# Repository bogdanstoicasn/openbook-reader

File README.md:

# OpenBook-reader

## Overview

OpenBook is an open-source e-book reader designed to be affordable and customizable. It is built around the ESP32-C6 microcontroller and integrates an E-Ink display, a Li-Po battery, and a microSD slot for extended storage. The device targets a wide range of users, from hobbyists to developers, who want to create their own e-book reader or modify existing designs.

## Table of Contents

1. [Features](#features)

2. [Data](#data)

3. [Block Diagram](#block-diagram)

4. [Hardware Functionality](#hardware-functionality)

5. [Hardware Components & Datasheets](#hardware-components--datasheets)

6. [Implementation](#implementation)

7. [Design Decisions and Trade-offs](#design-decisions-and-trade-offs)

8. [3D Visualizations](#3d-visualizations)
   
9. [Testing and Debugging](#testing-and-debugging)

10. [Suggestions](#suggestions)

## Features

- **Microcontroller**: ESP32-C6 with Wi-Fi and Bluetooth capabilities

- **Display**: 7.5" E-Ink display with a resolution of  800x480 pixels

- **Storage**: MicroSD card slot for additional storage

- **Battery**: Rechargeable Li-Po battery with a capacity of 2500mAh

- **Connectivity**: Wi-Fi 6, Bluetooth 5.0, and USB-C for charging and data transfer

- **Sensors**: Integrated environmental sensor (BME680) for temperature, humidity, pressure, and gas measurements

- **Real-Time Clock**: DS3231 for accurate timekeeping

- **User Interface**: 3 tactile buttons for navigation and control

## Data

Dimension: 175mm x 114mm x 10mm

Weight: 250g
Supported file formats: EPUB, PDF, TXT, FB2.

Operating system: FreeRTOS

Charging: 5V/1A via USB-C

## Block Diagram

## Hardware Functionality

### Microcontroller:

The ESP32-C6 is the main processing unit, responsible for handling all system operations, including e-paper display updates, wireless communication, and power management. It features:

- RISC-V architecture 32-bit core

- 2.4 GHz Wi-Fi and Bluetooth 5.0 connectivity

-  160 MHz clock speed with 4 stage pipeline

- L1 chache 16KB

- ROM 320KB

- SRAM 512KB(HP) + 16KB (LP)

- 30 GPIO pins

Power consumption: 160uA in deep sleep mode, 10mA in active mode

### Display:

- Type: E-Ink (E-Paper) display

- Size: 7.5 inches

- Resolution:  800x480 pixels

- Communication: SPI interface

- Power consumption: ~1.2mW in active mode, ~0.1mW in standby mode

Connection to the ESP32-C6 and other modules:

> IO7 -> MOSI(14)

> IO6 -> SCK(13)

> IO10 -> EPD_CS(12)

> IO5 -> EPD_DC(11)

> IO23 -> EPD_RST(10)

> IO3 -> EPD_BUSY(9)

Connection to power:

> EPD_3V3 -> 3.3V

### MicroSD Card

- Type: MicroSD card

- Capacity: Up to 32GB (FAT32 format)

- Communication: SPI interface

- Power consumption: ~50mA during read/write operations, ~10uA in standby mode

Connection to the ESP32-C6 and other modules:

> IO7 -> MOSI(CMD)

> IO6 -> SCK(CLK)

> IO4 -> SS_SD(CD/DAT3)

> IO2 -> MISO(DAT0)

### Battery and Power Management

- Type: Li-Po battery

- Capacity: 2500mAh

- Voltage: 3.7V nominal, 4.2V max

- Voltage regulator: MCP73831T for charging and power management

- Charging: 5V/1A via USB-C

- Power consumption: ~10mA during active mode, less than 50uA in deep sleep mode

Connection to the ESP32-C6 and other modules:

> CELL -> BAT

> IO21 -> SDA(SDA)

> IO22 -> SCL(SCL)

### Environmental Sensor

- Type: BME680

- Measurement: Temperature, humidity, pressure, and gas

- Communication: I2C interface

- Power consumption: ~3.6mA during measurement, ~0.1uA in sleep mode

Connection to the ESP32-C6 and other modules:

> IO21 -> SDA(SDI)

> IO22 -> SCL(SCK)

> IO19 -> I2C_PW(VDDIO)

### Real-Time Clock

- Type: DS3231

- Function: Accurate timekeeping

- Communication: I2C interface

- Power consumption: ~1.5uA in battery backup mode, ~0.1uA in sleep mode

Connection to the ESP32-C6 and other modules:

> IO21 -> SDA(15)

> IO22 -> SCL(16)

> IO18 -> RTC_RST(RST)

> IO1 -> 32KHz(32KHz)

> IO0 -> INT_RTC(SQW/INT)

### External Nor Flash

- Type: SPI Flash

- Capacity: 64MB

- Communication: SPI interface

- Power consumption: ~10mA during read/write operations, ~0.1uA in standby mode

Connection to the ESP32-C6 and other modules:

> IO11 -> EPD_CS(CS)

> IO6 -> SCK(CLK)

> IO2 -> MISO(DO/IO1)

> IO7 -> MOSI(DI/IO0)

### USB-C Connector

- Type: USB-C connector

- Function: Charging and data transfer

- Power consumption: ~5V/1A during charging, ~0.1uA in standby mode

- Protection: PFMF varistor for ESD protection

- Diode: Schottky barrier rectifier diode for reverse polarity protection

### Buttons

- Type: Tactile push buttons

- Number: 3

- Function: User input for navigation and control

Connection to the ESP32-C6 and other modules:

> EN -> RESET

> IO9 -> IO/BOOT

> IO15 -> IO/CHANGE

### Calculations

| Component | Current Draw (mA) | Voltage (V) | Power (mW) |
|-----------|-------------------|-------------|------------|
| ESP32-C6  | 10 | 3.3         | 33         |
| E-Ink Display | 1.2 | 3.3         | 3.96       |
| MicroSD Card | 50 | 3.3         | 165        |
| BME680 | 3.6 | 3.3         | 11.88      |
| DS3231 | 0.015 | 3.3         | 0.0495     |
| MCP73831T | 10 | 3.3         | 33         |
| USB-C Connector | 5 | 5         | 25         |
| External Flash | 10 | 3.3         | 33         |

Total Power Consumption: 304.3 mW
Total Current Draw: 89.8 mA

## Hardware Components & Datasheets

| Name | Description | Num | Datasheet | Price |
|------|-------------|-----|-----------|-------|
| Micro-SD | Micro-Sd | 1 | https://www.attend.com.tw/data/download/file/112A-TAAR-R03_Spec.pdf | https://www.digikey.com/en/products/detail/attend-technology/112A-TAAR-R03/17633923 |
| Inductor | 68uH | 1 | https://www.we-online.com/components/products/datasheet/784373170680.pdf | https://eu.mouser.com/ProductDetail/Wurth-Elektronik/784373170680?qs=sGAEpiMZZMv126LJFLh8yzGkpireax1GgDeN9GF1EUQ%3D |
| Led | No description | 1 | https://www.bridgelux.com/sites/default/files/resource_media/DS51_Rev%20F%20Bridgelux%20SMD%203030%20Data%20sheet.pdf | https://www.digikey.com/en/products/detail/bridgelux/BXEM-27E0000-0-000/6618599 |
| Voltage Detector | With Adjustable Delay Time | 1 | https://www.rohm.com/datasheet?p=BD5229G&dist=Digi-key&media=referral&source=digi-key.com&campaign=Digi-key | https://www.digikey.com/en/products/detail/rohm-semiconductor/BD5229G-TR/658502?s=N4IgTCBcDaIEIBECsYwE4DiBaAKgJRAF0BfIA |
| Buttons | No description | 3 | https://configured-product-images.s3.amazonaws.com/Datasheets/TL3315.pdf | https://www.digikey.com/en/products/detail/e-switch/TL3315NF250Q/1870396 |
| Super Capacitor | 0.011F 3.3V | 1 | https://mm.digikey.com/Volume0/opasdata/d220001/medias/docus/6537/rev05-CPHCPM.pdf | https://www.digikey.com/en/products/detail/seiko-instruments/cph3225a/8692444 |
| Real Time Clock | Serial 16-Pin SOIC | 1 | https://www.analog.com/media/en/technical-documentation/data-sheets/DS3231.pdf | https://www.digikey.com/en/products/detail/analog-devices-inc-maxim-integrated/DS3231SN/1197576 |
| Capacitor | 8 x 100uF + 6 x 4.7 uF + 1uF x 11 + 1 x 10uF -> Check this capacitor series(look at capacitance code to buy from the specs)| 26 | https://eu.mouser.com/datasheet/2/40/cx5r_KGM-3223198.pdf | https://eu.mouser.com/ProductDetail/KYOCERA-AVX/0402YD104MAT2A?qs=4PckX6MNpMErOINbbZj3Cw%3D%3D&srsltid=AfmBOorRllqAGFDVGSlUxRe1HCu5DEMiSSNplU-KeE2woDnCuT1J4_ia |
| ESP32-C6-WROOM-1-N8 | Microcontroller of choice | 1 | https://www.espressif.com/sites/default/files/documentation/esp32-c6-wroom-1_wroom-1u_datasheet_en.pdf | https://www.digikey.com/en/products/detail/espressif-systems/ESP32-C6-WROOM-1-N8/17728866?utm_source=snapeda&utm_campaign=buynow&utm_medium=aggregator |
| Varsistor | Used in the USB Connector zone | 1 | https://ro.mouser.com/datasheet/2/358/typ_PFMF-1275918.pdf | https://ro.mouser.com/ProductDetail/Schurter/PFMF.050.2?qs=1auRipcfynCums5v1iucSA%3D%3D |
| Diode | Schottky Barrier Rectifier Diode | 2 | https://datasheets.kyocera-avx.com/schottky.pdf | https://www.digikey.com/en/products/detail/kyocera-avx/sd0805s020s1r0/3749517 |
| Integrated Environmental Unit | Sensor | 1 | https://www.bosch-sensortec.com/media/boschsensortec/downloads/datasheets/bst-bme680-ds001.pdf | https://www.digikey.com/en/products/detail/bosch-sensortec/bme680/7401317 |
| Resistor | Search on DigiKey 0402 smd resistor x (size). The link contains both the site to but from and the datasheet in the order from 'Num' coloumn. |5K1 x 1 + 100K x 1 + 10K x 16 + 0.47 x 1 + 2K x 1 + 200 x 1 + 15 x 1 | [https://www.yageo.com/upload/media/product/products/datasheet/rchip/PYu-RC_Group_51_RoHS_L_12.pdf](https://www.digikey.com/en/products/detail/yageo/RC0402FR-075K1L/726624) - https://www.digikey.com/en/products/detail/yageo/RC0402JR-07100KL/726416 - https://www.digikey.com/en/products/detail/yageo/RC0402JR-0710KL/726418 - https://www.digikey.com/en/products/detail/cts-resistor-products/73L1R47J/1543472 - https://www.digikey.com/en/products/detail/panasonic-electronic-components/ERJ-2RKF2001X/192194 - https://www.digikey.com/en/products/detail/panasonic-electronic-components/ERJ-2RKF2000X/192215 - https://www.digikey.com/en/products/detail/panasonic-electronic-components/ERJ-2RKF15R0X/192142 | Check the 'Datasheet' section |
| P-channel MOSFETs | DMG2305UX-7 | 2 | https://www.diodes.com/assets/Datasheets/DMG2305UX.pdf | https://www.digikey.com/en/products/detail/diodes-incorporated/DMG2305UX-7/4340667 | 
| Li-Ion, Li-Pol Controller | MCP73831T | 1 | https://ww1.microchip.com/downloads/en/DeviceDoc/MCP73831-Family-Data-Sheet-DS20001984H.pdf | https://www.digikey.com/en/products/detail/microchip-technology/MCP73831T-2ACI-OT/964301 |
| Hirose Connector | 24 Position FFC, FPC Connector Contacts, Top and Bottom 0.020" (0.50mm) Surface Mount, Right Angle | 1 | https://ro.mouser.com/datasheet/2/185/FH34SRJ_24S_0_5SH_99__CL0580_1255_6_99_2DDrawing_0-1615044.pdf | https://ro.mouser.com/ProductDetail/Hirose-Connector/FH34SRJ-24S-0.5SH99?qs=vcbW%252B4%252BSTIpKBl5ap9J8Fw%3D%3D |
| Battery Monitor IC | 3µA 1-Cell/2-Cell Fuel Gauge with ModelGauge | 1 | https://datasheets.maximintegrated.com/en/ds/MAX17048-MAX17049.pdf | https://www.digikey.com/en/products/detail/analog-devices-inc-maxim-integrated/MAX17048G-T10/3758921?utm_source=snapeda&utm_campaign=buynow&utm_medium=aggregator |
| Diode | DIODE, SCHOTTKY, 0.5A, 30V, SOD-123 | 3 | https://ro.mouser.com/datasheet/2/258/MBR0520_MBR0580_SOD123_-2492194.pdf | https://ro.mouser.com/ProductDetail/Micro-Commercial-Components-MCC/MBR0530-TP?qs=KFo7JewZbUECRHkxGanrdg%3D%3D&utm_id=6470900573&utm_source=google&utm_medium=cpc&utm_marketing_tactic=emeacorp&gad_source=1&gclid=CjwKCAjwwLO_BhB2EiwAx2e-3ydGTTX86bQDTTakfn6ATmKxw6Z5gldNGNQk4bDz2SK5HmB7sD0ZQxoCdvQQAvD_BwE&_gl=1*1n24ce1*_ga*MTM0NDU1MzYwMi4xNzQzMjYxMTcy*_ga_15W4STQT4T*MTc0MzU5MDMwOC41LjEuMTc0MzU5MjU2NS4xOC4wLjA. |
| Diode | ESD Suppressor Diode Polymer Bi-Dir 24V 150Vc 2-Pin Case 0603(1608Metric) T/R | 6 | https://www.littelfuse.com/assetdocs/pulseguard-esd-suppressors-pgb1-datasheet?assetguid=8a337998-d54d-466b-be4e-dc5bcd1f9321 | https://www.digikey.com/en/products/detail/littelfuse-inc/PGB1010603MR/715755?utm_source=snapeda&utm_campaign=buynow&utm_medium=aggregator |
| Qwiic Connector | SparkFun I2C Standard Qwiic Connector | 1 | Check https://www.sparkfun.com/qwiic | https://www.digikey.com/en/products/detail/onion-corporation/om-e-qwiic/9922970 |
| Capacitor | Polarized, 0.5pF ~ 100uF | 1 | https://ro.mouser.com/datasheet/2/281/1/GCQ1555C1HR50WB01_01A-3146956.pdf | https://ro.mouser.com/ProductDetail/Murata-Electronics/GCQ1555C1HR50WB01D?qs=0lQeLiL1qybSG%2FOlONlvIA%3D%3D |
| Connector USB | CONN USB 2.0 TYPE-C R/A SMT | 1 | https://gct.co/files/drawings/usb4110.pdf | https://eu.mouser.com/ProductDetail/GCT/USB4110-GF-A?qs=KUoIvG%2F9IlYiZvIXQjyJeA%3D%3D&utm_id=6470900573&utm_source=google&utm_medium=cpc&utm_marketing_tactic=emeacorp&gad_source=1&gclid=CjwKCAjwwLO_BhB2EiwAx2e-37JzTMkPOyYe_IgHkPGbT94lZUm900GBIAmoPtrMJZJCTbY6hQYkwBoChsQQAvD_BwE |
| N-channel MOSFETs | Mosfet N-Channel 30 V 1.4A (Tc) 400mW (Ta), 500mW (Tc) Surface Mount SC-70-3 (SI1308EDL-T1-GE3)| 1 | https://www.vishay.com/docs/63399/si1308edl.pdf | https://www.digikey.com/en/products/detail/vishay-siliconix/si1308edl-t1-ge3/4876435 |
| Solder Jumper | We can use 0 ohms resistor | 1 | https://industrial.panasonic.com/ww/products/pt/general-purpose-chip-resistors/models/ERJ2GE0R00X | https://www.digikey.com/en/products/detail/panasonic-electronic-components/ERJ-2GE0R00X/146727 |
| Test Pad | Testing points for the PCB (Adafruit). | 17 | https://analytics.supplyframe.com/trackingservlet/track/?r=0x34EY99PS_gIu2qWuzU9_U842M9-un2szqNoXX0OQ9lqbiEKGN3BJ73jgvlrgiXR89Peb0evqc4GXoUXllBhu1MMSvPYuTjdNvrqssrdYelKlOnXRLLdDb62WVGcgff9ScDqkaNl77wLfnOOEQKj2STWkPX13L-FNZ3oWIMFUHCC5-qDG-7Yig6Avs38Cl7gJvFvhhIZBQgwOTPSvwankeiqCZiPIu4pf1a70cDpS5iXBHs4MnmfZND2GG-sF6aJg5UUnsB5VhTJSE6wk45p-6HRTMw22O4bszSnP2Q-ZnkBbKsUJKjNCqwjgBsJDq1_QscdqTO6PxRf527DX_uye2RbWidMqOlR-Vbcwp2OFH8GWfRIZFBGLsZvpqmkT4i-YX6Nptn2BWY2qtOQUnzCPdCvB7YMhgJaZgpVomGW3xiBrXHrx7fYI1m3zFYuPc18lUM4dLxlLjbOFrCL0NYDVpEveG92dFwHfnYbXQgvjrXr2rAOwFVNwEcAFSYk5ktrRa9hExtgpErVY2QODMhmvQzib95lr7oG9joYEr_b8joW8nw_gi1w2cyDxUshEAF | https://componentsearchengine.com/prices/3825?manufacturer=Adafruit |

## Implementation

### Initial Setup and Tool Selection

- Choose your PCB design software(Fusion360)

- Prepare the mechanical dimensions and casing files provided

### Create the Schematic

- Add the ESP32-C6 microcontroller, power components, display interfaces, buttons, and other required components

- Ensure the pin configuration for the ESP32-C6 matches the required hardware interfaces (e.g., SPI for the display, I2C for sensors).

- Implement decoupling capacitors near the power pins

- Electrical Design Validation (EVT)

### PCB Layout Design

- Place major components like the ESP32, display, and battery connectors according to the provided layout recommendations

- Route the traces carefully, avoiding sharp angles and placing vias in non-critical signal paths

- Design Rule Check(DRC)

### Mechanical Design Integration

- Create 3D models for case, battery and display for integration

- Verify that all components fit within the casing and that connectors like USB and SD card slots align with physical cutouts

## Design Decisions and Trade-offs

- Decoupling capacitors(100nF) should be placed close to the power pins of major components.

- Power traces width: 0.3mm

- Power traces were routed without vias to ensure low impedance and reliable power delivery.

- Signal traces width: 0.15mm

- No routing under ESP antenna.

- 2 layers PCB with 2 ground planes.

- All components on TOP Layer.

- Test pads were placed close to the relevant signals to facilitate easier probing and debugging.

- PCB cut near ESP32-C6 antenna for better signal, with a keep-out zone to reduce interference.

- The ESP32-C6 features multiple low-power modes (including deep sleep and light sleep) and efficient power domain management.

- Via stitching under the ESP32-C6 is beneficial for improving thermal dissipation and electromagnetic interference (EMI) performance.

- The PCB layout follows the reference design shown in Images/layout_reference.pdf.

- All PCB traces are routed to avoid 90-degree angles to ensure signal integrity and reduce the risk of electromagnetic interference (EMI).

- The 3D connection model for the display has been designed to provide a realistic representation of the **Display**; however, the connection model it's not flexible(used just for accurate display representation).

- The models for the battery and display are included to mimic their real-world sizes for visualization purposes. They do not reflect the actual hardware functionality or internal components.

- Integrating ESD protection helps safeguard sensitive components—like the ESP32-C6 and display driver—from electrostatic discharge events

## 3D Visualizations

### PCB

### Battery

### Display

### Full Product

## Testing and Debugging

The OpenBook PCB has test pads for each major communication and power line.

1. TPRX - RX signal
2. TPTX - TX signal
3. TPVBAT - Battery voltage
4. 2 x TPGND - Ground
5. TP3V3 - 3.3V power
6. TPEPD_3V3 - EPD 3.3V power
7. TPMISO - MISO signal
8. TPMOSI - MOSI signal
9. TPSCK - SCK signal
10. TPEPDBUSY - EPD BUSY signal
11. TPEPDCS - EPD CS signal
12. TPEPDDC - EPD DC signal
13. TPEPDRST - EPD RST signal
14. TPEPD3V3C - EPD 3.3V power
15. TPVBUS - VBUS voltage
16. TPINTRTC - RTC interrupt signal

## Suggestions

- Operating system: FreeRTOS

- Programming language: C/C++

- IDE: PlatformIO or Arduino IDE

- Libraries: ESP-IDF, EPD library, SD card library, BME680 library, DS3231 library

- Communication protocols: SPI, I2C, UART

- Power management: Use deep sleep mode to save power when not in use

- User interface: Use a simple menu system for navigation and control

- File management: Implement a file system for easy access to e-books on the microSD card

- E-book reader software: Use an existing open-source e-book reader software or develop a custom solution

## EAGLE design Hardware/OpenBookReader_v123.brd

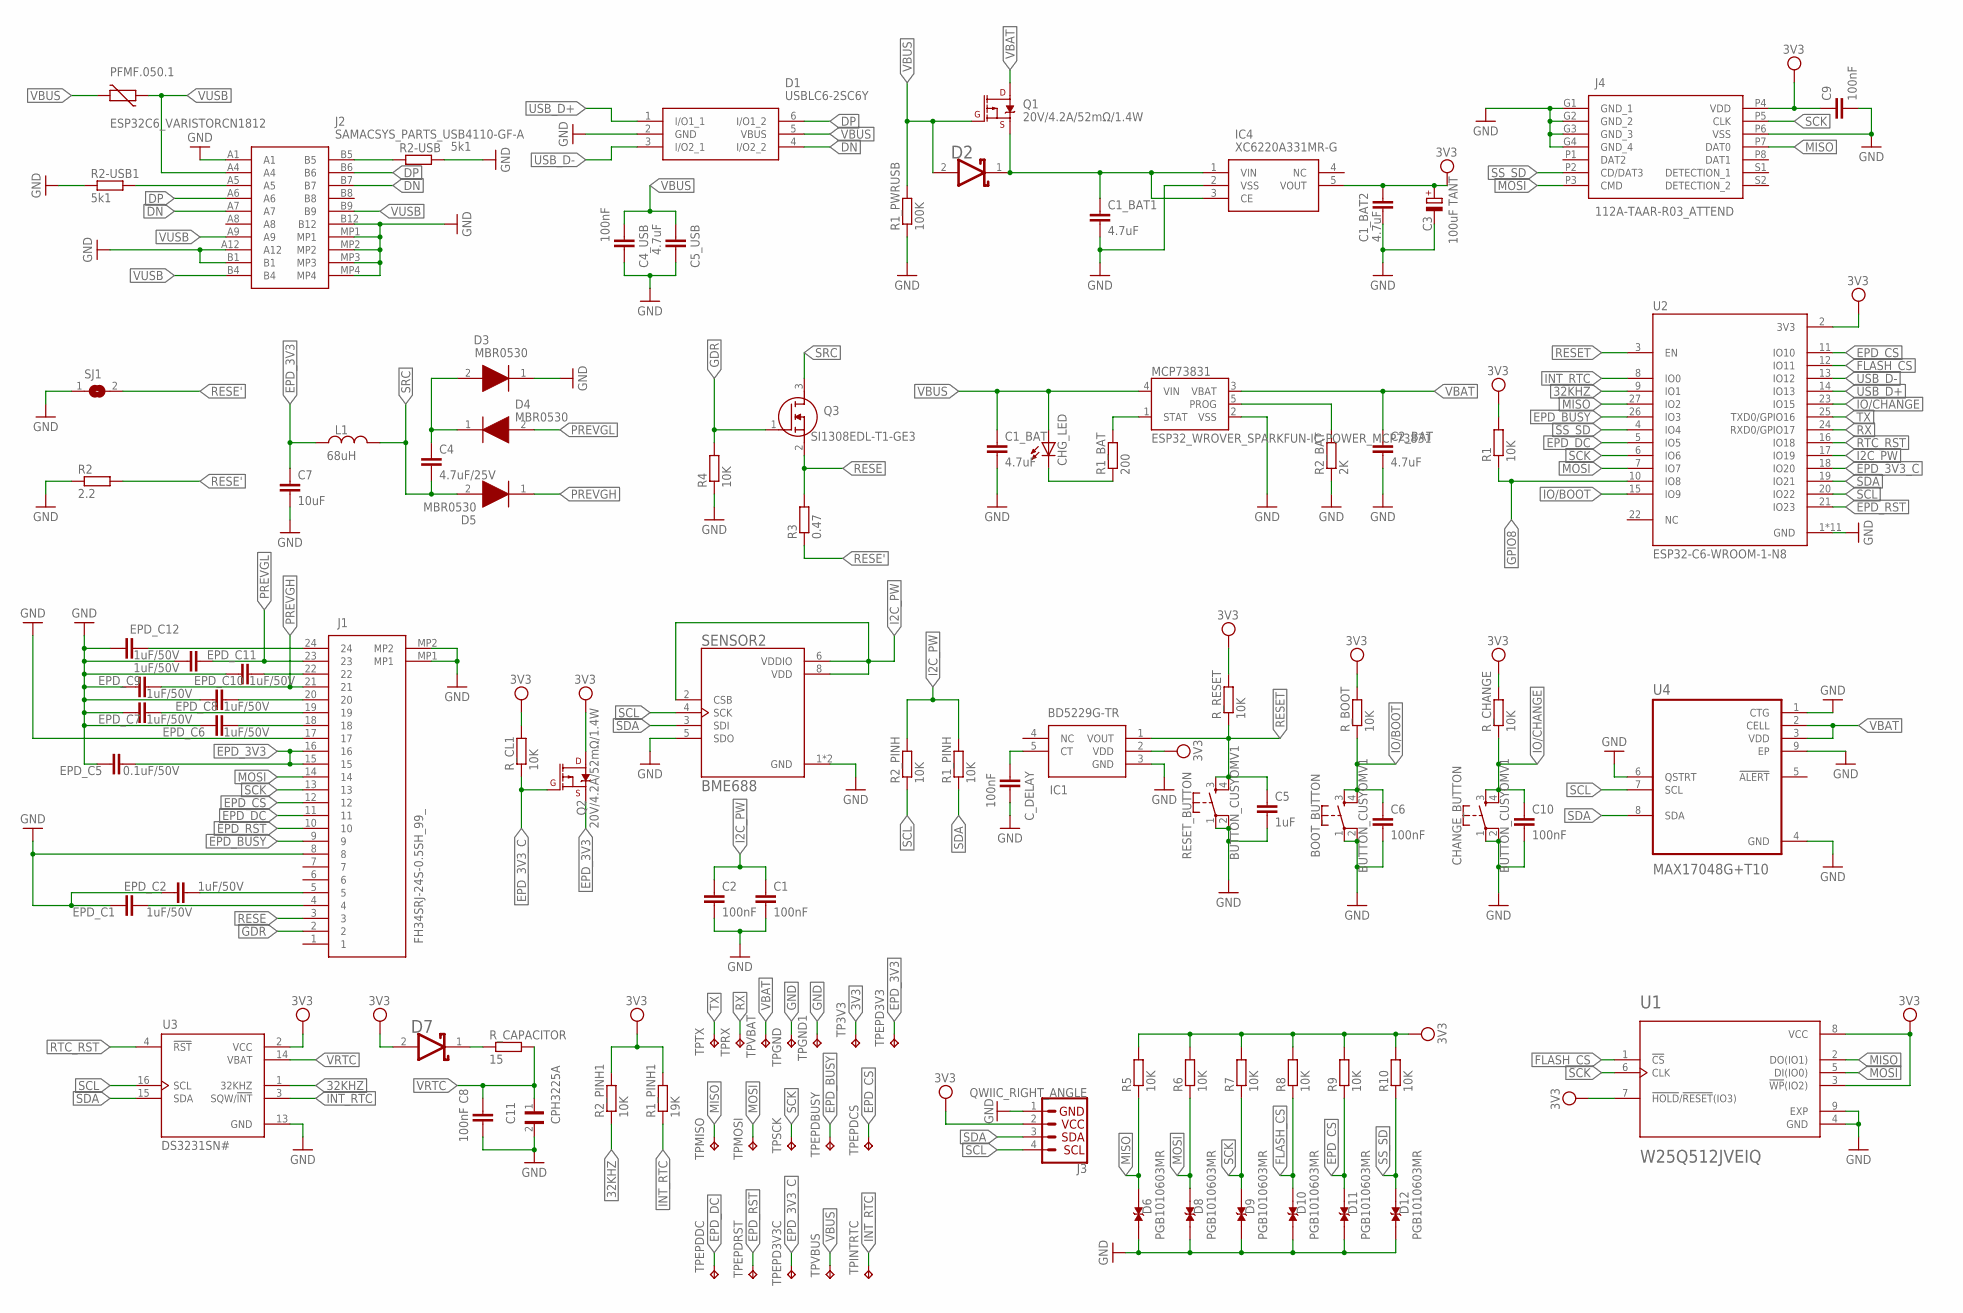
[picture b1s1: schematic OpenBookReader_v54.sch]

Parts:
BOOT_BUTTON: BUTTON_CUSYOMV1; MYBUTTON
C1, C2, C4_USB, C6, C8, C9, C10: 100nF; EAGLE-LTSPICE_C0402
C1_BAT, C1_BAT1, C1_BAT2, C2_BAT, C5_USB: 4.7uF; EAGLE-LTSPICE_C0402
C3: 100uF TANT; RCL_CT3528
C4: 4.7uF/25V; EAGLE-LTSPICE_C0402
C5: 1uF; EAGLE-LTSPICE_C0402
C7: 10uF; EAGLE-LTSPICE_C0402
C11: CPH3225A; CAPCP3225X100N
CHANGE_BUTTON: BUTTON_CUSYOMV1; MYBUTTON
CHG_LED: ADAFRUIT_LEDCHIP-LED0603; ADAFRUIT_CHIP-LED0603
C_DELAY: 100nF; EAGLE-LTSPICE_C0402
D1: USBLC6-2SC6Y; SOT95P280X145-6N
D2, D7: ESP32_WROVER_AVX---SD0805S020S1R0_AVX_SD0805S020S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; ESP32_WROVER_AVX---SD0805S020S1R0_AVX_SD0805S020S1R0_0
D3, D4, D5: MBR0530; SOD3716X135N
D6, D8, D9, D10, D11, D12: PGB1010603MR; DIOC1608X36N
EPD_C1, EPD_C2, EPD_C6, EPD_C7, EPD_C8, EPD_C9, EPD_C10, EPD_C11, EPD_C12: 1uF/50V; EAGLE-LTSPICE_C0402
EPD_C5: 0.1uF/50V; EAGLE-LTSPICE_C0402
IC1: BD5229G-TR; SOT95P280X125-5N
IC4: XC6220A331MR-G; SOT95P280X120-5N
J1: FH34SRJ-24S-0.5SH_99_; FH34SRJ24S05SH99
J2: SAMACSYS_PARTS_USB4110-GF-A; SAMACSYS_PARTS_USB4110GFA
J3: QWIIC_RIGHT_ANGLE; JST04_1MM_RA
J4: 112A-TAAR-R03_ATTEND; 112ATAARR03ATTEND
L1: 68uH; INDC1006X60N
MCP73831: ESP32_WROVER_SPARKFUN-IC-POWER_MCP73831; ESP32_WROVER_SPARKFUN-IC-POWER_SOT23-5
PFMF.050.1: ESP32C6_VARISTORCN1812; ESP32C6_VARISTOR_CT/CN1812
Q1, Q2: 20V/4.2A/52mΩ/1.4W; ESP32_WROVER_SPARKFUN-DISCRETESEMI_SOT23-3
Q3: SI1308EDL-T1-GE3; SOT65P210X110-3N
R1, R1_PINH, R2_PINH, R2_PINH1, R4, R5, R6, R7, R8, R9, R10: 10K; ESP32_WROVER_EAGLE-LTSPICE_R0402
R1_BAT: 200; ESP32_WROVER_EAGLE-LTSPICE_R0402
R1_PINH1: 19K; ESP32_WROVER_EAGLE-LTSPICE_R0402
R1_PWRUSB: 100K; ESP32_WROVER_EAGLE-LTSPICE_R0402
R2: 2.2; ESP32_WROVER_EAGLE-LTSPICE_R0402
R2-USB, R2-USB1: 5k1; ESP32_WROVER_EAGLE-LTSPICE_R0402
R2_BAT: 2K; ESP32_WROVER_EAGLE-LTSPICE_R0402
R3: 0.47; ESP32_WROVER_EAGLE-LTSPICE_R0402
RESET_BUTTON: BUTTON_CUSYOMV1; MYBUTTON
R_BOOT: 10K; ESP32_WROVER_EAGLE-LTSPICE_R0402
R_CAPACITOR: 15; ESP32_WROVER_EAGLE-LTSPICE_R0402
R_CHANGE: 10K; ESP32_WROVER_EAGLE-LTSPICE_R0402
R_CL1: 10K; ESP32_WROVER_EAGLE-LTSPICE_R0402
R_RESET: 10K; ESP32_WROVER_EAGLE-LTSPICE_R0402
SENSOR2: BME688; ESP32_WROVER_BME680_PSON80P300X300X100-8N
SJ1: SJ
TP3V3: TPTP20R; TP20R
TPEPD3V3, TPEPD3V3C: TPTP20R; TP20R
TPEPDBUSY: TPTP20R; TP20R
TPEPDCS: TPTP20R; TP20R
TPEPDDC: TPTP20R; TP20R
TPEPDRST: TPTP20R; TP20R
TPGND, TPGND1: TPTP20R; TP20R
TPINTRTC: TPTP20R; TP20R
TPMISO: TPTP20R; TP20R
TPMOSI: TPTP20R; TP20R
TPRX: TPTP20R; TP20R
TPSCK: TPTP20R; TP20R
TPTX: TPTP20R; TP20R
TPVBAT: TPTP20R; TP20R
TPVBUS: TPTP20R; TP20R
U1: W25Q512JVEIQ; SON127P600X800X80-9N
U2: ESP32-C6-WROOM-1-N8; XCVR_ESP32-C6-WROOM-1-N8
U3: DS3231SN#; SOIC127P1032X265-16N
U4: MAX17048G+T10; SON50P200X200X80-9N

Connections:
3V3: C1_BAT2.1, C3.+, C9.1, D7.2 (ANODE), IC1.2 (VDD), IC4.5 (VOUT), J3.2, J4.P4 (VDD), Q2.3 (D), R1.2, R1_PINH1.2, R2_PINH1.2, R5.2, R6.2, R7.2, R8.2, R9.2, R10.2, R_BOOT.2, R_CHANGE.2, R_CL1.2, R_RESET.2, TP3V3.TP, U1.3 (!WP!(IO2)), U1.7 (!HOLD!/!RESET!(IO3)), U1.8 (VCC), U2.2 (3V3), U3.2 (VCC)
32KHZ: R2_PINH1.1, U2.9 (IO1), U3.1 (32KHZ)
DN: D1.4 (I/O2_2), J2.A7, J2.B7
DP: D1.6 (I/O1_2), J2.A6, J2.B6
EPD_3V3: C7.1, EPD_C5.2, J1.15, J1.16, L1.1, Q2.2 (S), TPEPD3V3.TP
EPD_3V3_C: Q2.1 (G), R_CL1.1, TPEPD3V3C.TP, U2.18 (IO20)
EPD_BUSY: J1.9, TPEPDBUSY.TP, U2.26 (IO3)
EPD_CS: D11.2, J1.12, R9.1, TPEPDCS.TP, U2.11 (IO10)
EPD_DC: J1.11, TPEPDDC.TP, U2.5 (IO5)
EPD_RST: J1.10, TPEPDRST.TP, U2.21 (IO23)
FLASH_CS: D10.2, R8.1, U1.1 (!CS), U2.12 (IO11)
GDR: J1.2, Q3.1 (G), R4.2
GND: BOOT_BUTTON.1, BOOT_BUTTON.2, C1.2, C1_BAT.2, C1_BAT1.2, C1_BAT2.2, C2.2, C2_BAT.2, C3.-, C4_USB.2, C5.2, C5_USB.2, C6.2, C7.2, C8.2, C9.2, C10.2, C11.2, CHANGE_BUTTON.1, CHANGE_BUTTON.2, C_DELAY.2, D1.2 (GND), D3.1 (K), D6.1, D8.1, D9.1, D10.1, D11.1, D12.1, EPD_C1.1, EPD_C2.1, EPD_C5.1, EPD_C6.1, EPD_C7.1, EPD_C8.1, EPD_C9.1, EPD_C10.1, EPD_C11.1, EPD_C12.1, IC1.3 (GND), IC4.2 (VSS), J1.8, J1.17, J1.MP1, J1.MP2, J2.A1, J2.A12, J2.B1, J2.B12, J2.MP1, J2.MP2, J2.MP3, J2.MP4, J3.1, J4.G1 (GND_1), J4.G2 (GND_2), J4.G3 (GND_3), J4.G4 (GND_4), J4.P6 (VSS), MCP73831.2 (VSS), R1_PWRUSB.1, R2.1, R2-USB.2, R2-USB1.1, R2_BAT.1, R4.1, RESET_BUTTON.1, RESET_BUTTON.2, SENSOR2.1 (GND), SENSOR2.5 (SDO), SENSOR2.7 (GND), SJ1.1, TPGND.TP, TPGND1.TP, U1.4 (GND), U1.9 (EXP), U2.1 (GND), U2.28 (GND), U2.29_1 (GND), U2.29_2 (GND), U2.29_3 (GND), U2.29_4 (GND), U2.29_5 (GND), U2.29_6 (GND), U2.29_7 (GND), U2.29_8 (GND), U2.29_9 (GND), U3.13 (GND), U4.1 (CTG), U4.4 (GND), U4.6 (QSTRT), U4.9 (EP)
GPIO8: R1.1, U2.10 (IO8)
I2C_PW: C1.1, C2.1, R1_PINH.2, R2_PINH.2, SENSOR2.2 (CSB), SENSOR2.6 (VDDIO), SENSOR2.8 (VDD), U2.17 (IO19)
INT_RTC: R1_PINH1.1, TPINTRTC.TP, U2.8 (IO0), U3.3 (SQW/!INT)
IO/BOOT: BOOT_BUTTON.3, BOOT_BUTTON.4, C6.1, R_BOOT.1, U2.15 (IO9)
IO/CHANGE: C10.1, CHANGE_BUTTON.3, CHANGE_BUTTON.4, R_CHANGE.1, U2.23 (IO15)
MISO: D6.2, J4.P7 (DAT0), R5.1, TPMISO.TP, U1.2 (DO(IO1)), U2.27 (IO2)
MOSI: D8.2, J1.14, J4.P3 (CMD), R6.1, TPMOSI.TP, U1.5 (DI(IO0)), U2.7 (IO7)
unnamed: J2.A5, R2-USB1.2
unnamed: J2.B5, R2-USB.1
unnamed: C1_BAT1.1, D2.1 (CATHODE), IC4.1 (VIN), IC4.3 (CE), Q1.2 (S)
unnamed: MCP73831.1 (STAT), R1_BAT.2
unnamed: C4.1, D3.2 (A), D4.1 (K)
unnamed: CHG_LED.C, R1_BAT.1
unnamed: MCP73831.5 (PROG), R2_BAT.2
unnamed: EPD_C12.2, J1.24
unnamed: EPD_C10.2, J1.22
unnamed: EPD_C8.2, J1.20
unnamed: EPD_C7.2, J1.19
unnamed: EPD_C6.2, J1.18
unnamed: EPD_C2.2, J1.5
unnamed: EPD_C1.2, J1.4
unnamed: C_DELAY.1, IC1.5 (CT)
unnamed: D7.1 (CATHODE), R_CAPACITOR.1
PREVGH: D5.1 (K), EPD_C9.2, J1.21
PREVGL: D4.2 (A), EPD_C11.2, J1.23
RESE: J1.3, Q3.2 (S), R3.2
RESE': R2.2, R3.1, SJ1.2
RESET: C5.1, IC1.1 (VOUT), RESET_BUTTON.3, RESET_BUTTON.4, R_RESET.1, U2.3 (EN)
RTC_RST: U2.16 (IO18), U3.4 (!RST)
RX: TPRX.TP, U2.24 (RXD0/GPIO17)
SCK: D9.2, J1.13, J4.P5 (CLK), R7.1, TPSCK.TP, U1.6 (CLK), U2.6 (IO6)
SCL: J3.4, R2_PINH.1, SENSOR2.4 (SCK), U2.20 (IO22), U3.16 (SCL), U4.7 (SCL)
SDA: J3.3, R1_PINH.1, SENSOR2.3 (SDI), U2.19 (IO21), U3.15 (SDA), U4.8 (SDA)
SRC: C4.2, D5.2 (A), L1.2, Q3.3 (D)
SS_SD: D12.2, J4.P2 (CD/DAT3), R10.1, U2.4 (IO4)
TX: TPTX.TP, U2.25 (TXD0/GPIO16)
USB_D+: D1.1 (I/O1_1), U2.14 (IO13)
USB_D-: D1.3 (I/O2_1), U2.13 (IO12)
VBAT: C2_BAT.1, MCP73831.3 (VBAT), Q1.3 (D), TPVBAT.TP, U4.2 (CELL), U4.3 (VDD)
VBUS: C1_BAT.1, C4_USB.1, C5_USB.1, CHG_LED.A, D1.5 (VBUS), D2.2 (ANODE), MCP73831.4 (VIN), PFMF.050.1.2, Q1.1 (G), R1_PWRUSB.2, TPVBUS.TP
VRTC: C8.1, C11.1, R_CAPACITOR.2, U3.14 (VBAT)
VUSB: J2.A4, J2.A9, J2.B4, J2.B9, PFMF.050.1.1

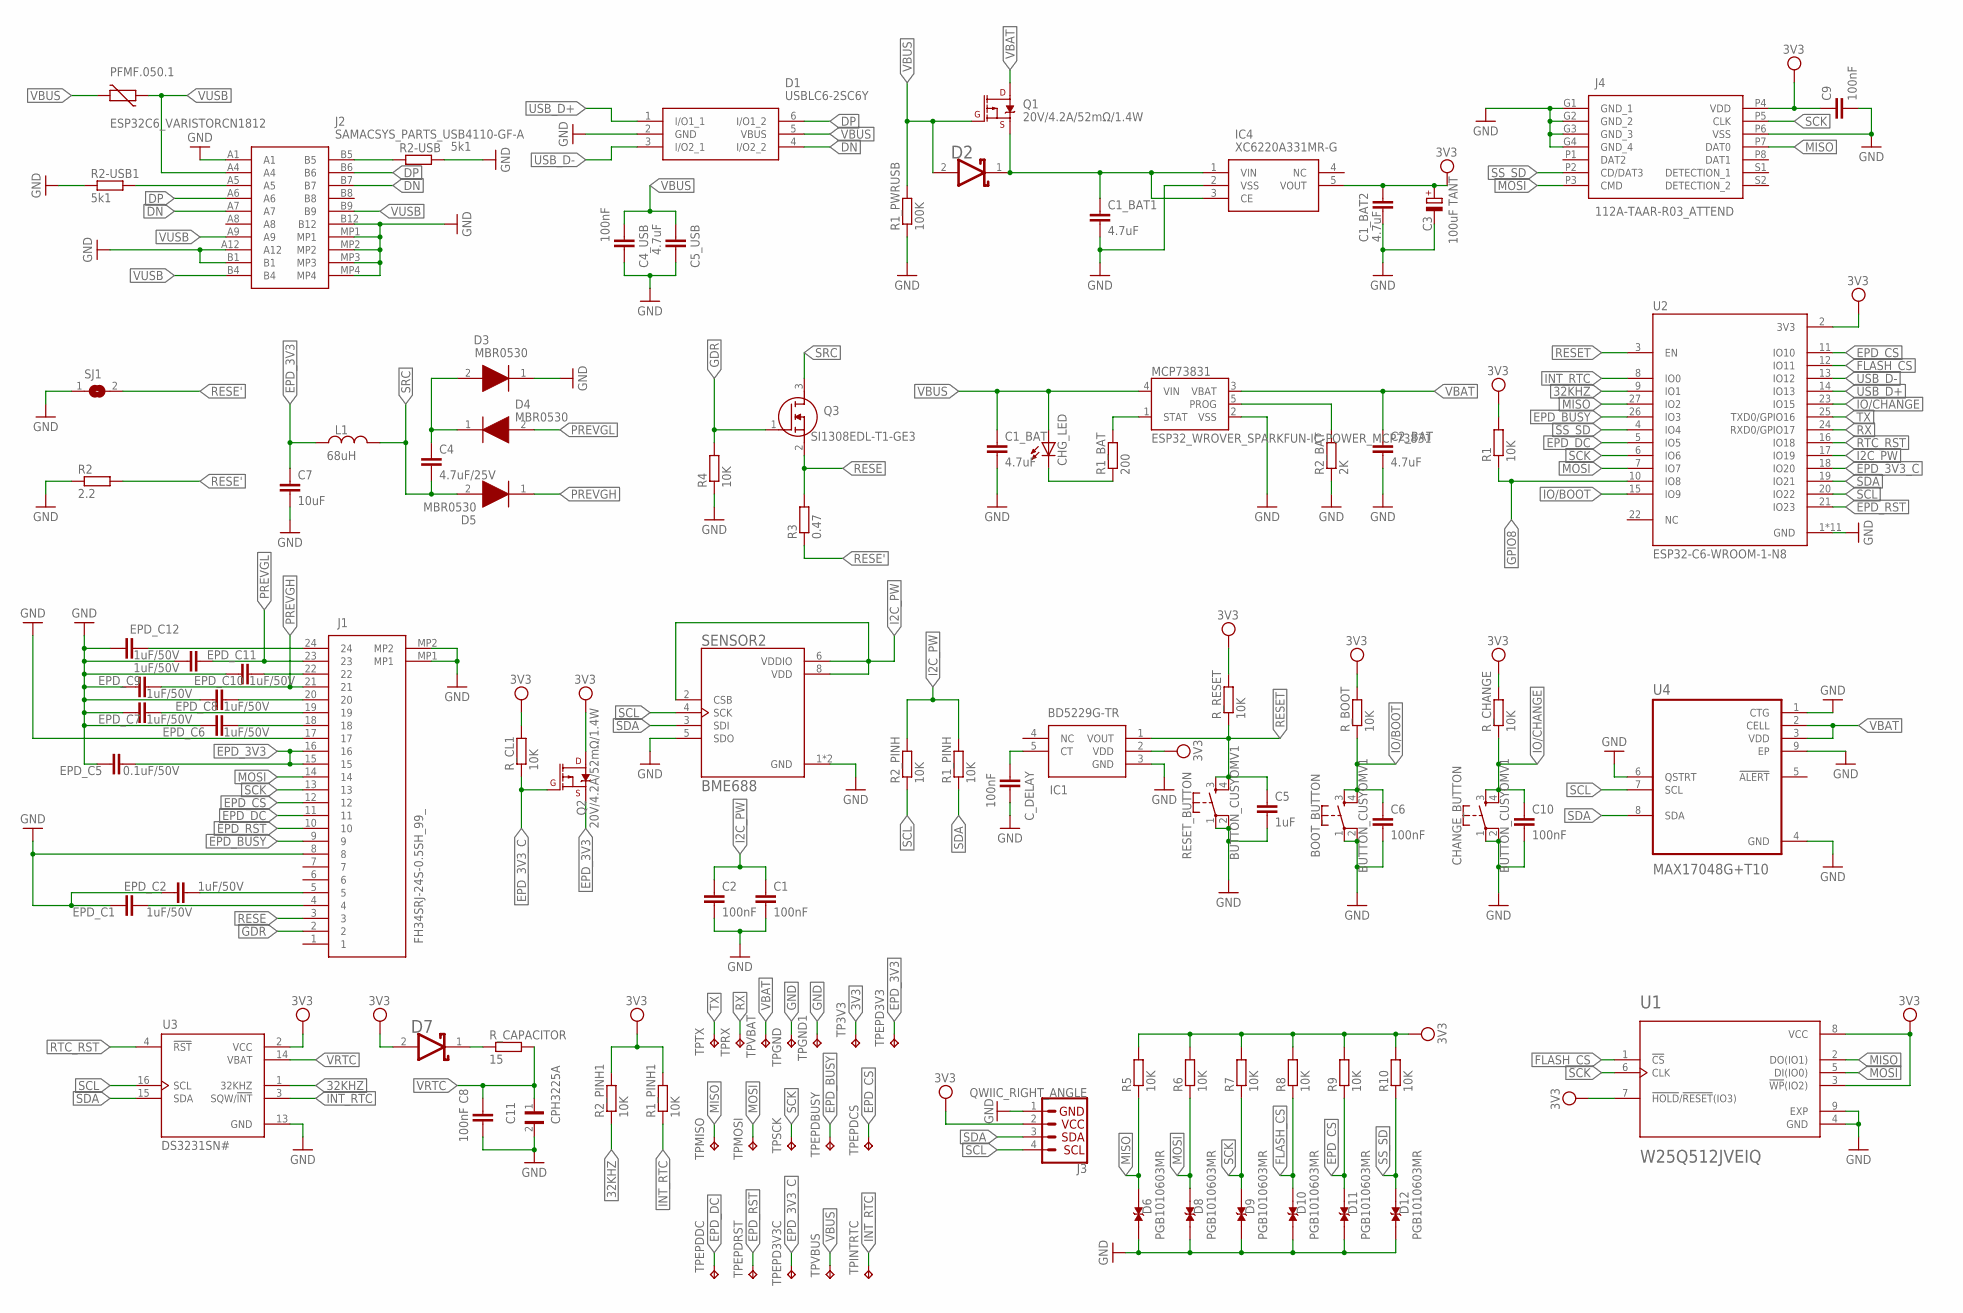
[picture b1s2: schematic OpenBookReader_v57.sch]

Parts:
BOOT_BUTTON: BUTTON_CUSYOMV1; MYBUTTON
C1, C2, C4_USB, C6, C8, C9, C10: 100nF; EAGLE-LTSPICE_C0402
C1_BAT, C1_BAT1, C1_BAT2, C2_BAT, C5_USB: 4.7uF; EAGLE-LTSPICE_C0402
C3: 100uF TANT; RCL_CT3528
C4: 4.7uF/25V; EAGLE-LTSPICE_C0402
C5: 1uF; EAGLE-LTSPICE_C0402
C7: 10uF; EAGLE-LTSPICE_C0402
C11: CPH3225A; CAPCP3225X100N
CHANGE_BUTTON: BUTTON_CUSYOMV1; MYBUTTON
CHG_LED: ADAFRUIT_LEDCHIP-LED0603; ADAFRUIT_CHIP-LED0603
C_DELAY: 100nF; EAGLE-LTSPICE_C0402
D1: USBLC6-2SC6Y; SOT95P280X145-6N
D2, D7: ESP32_WROVER_AVX---SD0805S020S1R0_AVX_SD0805S020S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; ESP32_WROVER_AVX---SD0805S020S1R0_AVX_SD0805S020S1R0_0
D3, D4, D5: MBR0530; SOD3716X135N
D6, D8, D9, D10, D11, D12: PGB1010603MR; DIOC1608X36N
EPD_C1, EPD_C2, EPD_C6, EPD_C7, EPD_C8, EPD_C9, EPD_C10, EPD_C11, EPD_C12: 1uF/50V; EAGLE-LTSPICE_C0402
EPD_C5: 0.1uF/50V; EAGLE-LTSPICE_C0402
IC1: BD5229G-TR; SOT95P280X125-5N
IC4: XC6220A331MR-G; SOT95P280X120-5N
J1: FH34SRJ-24S-0.5SH_99_; FH34SRJ24S05SH99
J2: SAMACSYS_PARTS_USB4110-GF-A; SAMACSYS_PARTS_USB4110GFA
J3: QWIIC_RIGHT_ANGLE; JST04_1MM_RA
J4: 112A-TAAR-R03_ATTEND; 112ATAARR03ATTEND
L1: 68uH; INDC1006X60N
MCP73831: ESP32_WROVER_SPARKFUN-IC-POWER_MCP73831; ESP32_WROVER_SPARKFUN-IC-POWER_SOT23-5
PFMF.050.1: ESP32C6_VARISTORCN1812; ESP32C6_VARISTOR_CT/CN1812
Q1, Q2: 20V/4.2A/52mΩ/1.4W; ESP32_WROVER_SPARKFUN-DISCRETESEMI_SOT23-3
Q3: SI1308EDL-T1-GE3; SOT65P210X110-3N
R1, R1_PINH, R1_PINH1, R2_PINH, R2_PINH1, R4, R5, R6, R7, R8, R9, R10: 10K; ESP32_WROVER_EAGLE-LTSPICE_R0402
R1_BAT: 200; ESP32_WROVER_EAGLE-LTSPICE_R0402
R1_PWRUSB: 100K; ESP32_WROVER_EAGLE-LTSPICE_R0402
R2: 2.2; ESP32_WROVER_EAGLE-LTSPICE_R0402
R2-USB, R2-USB1: 5k1; ESP32_WROVER_EAGLE-LTSPICE_R0402
R2_BAT: 2K; ESP32_WROVER_EAGLE-LTSPICE_R0402
R3: 0.47; ESP32_WROVER_EAGLE-LTSPICE_R0402
RESET_BUTTON: BUTTON_CUSYOMV1; MYBUTTON
R_BOOT: 10K; ESP32_WROVER_EAGLE-LTSPICE_R0402
R_CAPACITOR: 15; ESP32_WROVER_EAGLE-LTSPICE_R0402
R_CHANGE: 10K; ESP32_WROVER_EAGLE-LTSPICE_R0402
R_CL1: 10K; ESP32_WROVER_EAGLE-LTSPICE_R0402
R_RESET: 10K; ESP32_WROVER_EAGLE-LTSPICE_R0402
SENSOR2: BME688; ESP32_WROVER_BME680_PSON80P300X300X100-8N
SJ1: SJ
TP3V3: TPTP20R; TP20R
TPEPD3V3, TPEPD3V3C: TPTP20R; TP20R
TPEPDBUSY: TPTP20R; TP20R
TPEPDCS: TPTP20R; TP20R
TPEPDDC: TPTP20R; TP20R
TPEPDRST: TPTP20R; TP20R
TPGND, TPGND1: TPTP20R; TP20R
TPINTRTC: TPTP20R; TP20R
TPMISO: TPTP20R; TP20R
TPMOSI: TPTP20R; TP20R
TPRX: TPTP20R; TP20R
TPSCK: TPTP20R; TP20R
TPTX: TPTP20R; TP20R
TPVBAT: TPTP20R; TP20R
TPVBUS: TPTP20R; TP20R
U1: W25Q512JVEIQ; SON127P600X800X80-9N
U2: ESP32-C6-WROOM-1-N8; XCVR_ESP32-C6-WROOM-1-N8
U3: DS3231SN#; SOIC127P1032X265-16N
U4: MAX17048G+T10; SON50P200X200X80-9N

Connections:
3V3: C1_BAT2.1, C3.+, C9.1, D7.2 (ANODE), IC1.2 (VDD), IC4.5 (VOUT), J3.2, J4.P4 (VDD), Q2.3 (D), R1.2, R1_PINH1.2, R2_PINH1.2, R5.2, R6.2, R7.2, R8.2, R9.2, R10.2, R_BOOT.2, R_CHANGE.2, R_CL1.2, R_RESET.2, TP3V3.TP, U1.3 (!WP!(IO2)), U1.7 (!HOLD!/!RESET!(IO3)), U1.8 (VCC), U2.2 (3V3), U3.2 (VCC)
32KHZ: R2_PINH1.1, U2.9 (IO1), U3.1 (32KHZ)
DN: D1.4 (I/O2_2), J2.A7, J2.B7
DP: D1.6 (I/O1_2), J2.A6, J2.B6
EPD_3V3: C7.1, EPD_C5.2, J1.15, J1.16, L1.1, Q2.2 (S), TPEPD3V3.TP
EPD_3V3_C: Q2.1 (G), R_CL1.1, TPEPD3V3C.TP, U2.18 (IO20)
EPD_BUSY: J1.9, TPEPDBUSY.TP, U2.26 (IO3)
EPD_CS: D11.2, J1.12, R9.1, TPEPDCS.TP, U2.11 (IO10)
EPD_DC: J1.11, TPEPDDC.TP, U2.5 (IO5)
EPD_RST: J1.10, TPEPDRST.TP, U2.21 (IO23)
FLASH_CS: D10.2, R8.1, U1.1 (!CS), U2.12 (IO11)
GDR: J1.2, Q3.1 (G), R4.2
GND: BOOT_BUTTON.1, BOOT_BUTTON.2, C1.2, C1_BAT.2, C1_BAT1.2, C1_BAT2.2, C2.2, C2_BAT.2, C3.-, C4_USB.2, C5.2, C5_USB.2, C6.2, C7.2, C8.2, C9.2, C10.2, C11.2, CHANGE_BUTTON.1, CHANGE_BUTTON.2, C_DELAY.2, D1.2 (GND), D3.1 (K), D6.1, D8.1, D9.1, D10.1, D11.1, D12.1, EPD_C1.1, EPD_C2.1, EPD_C5.1, EPD_C6.1, EPD_C7.1, EPD_C8.1, EPD_C9.1, EPD_C10.1, EPD_C11.1, EPD_C12.1, IC1.3 (GND), IC4.2 (VSS), J1.8, J1.17, J1.MP1, J1.MP2, J2.A1, J2.A12, J2.B1, J2.B12, J2.MP1, J2.MP2, J2.MP3, J2.MP4, J3.1, J4.G1 (GND_1), J4.G2 (GND_2), J4.G3 (GND_3), J4.G4 (GND_4), J4.P6 (VSS), MCP73831.2 (VSS), R1_PWRUSB.1, R2.1, R2-USB.2, R2-USB1.1, R2_BAT.1, R4.1, RESET_BUTTON.1, RESET_BUTTON.2, SENSOR2.1 (GND), SENSOR2.5 (SDO), SENSOR2.7 (GND), SJ1.1, TPGND.TP, TPGND1.TP, U1.4 (GND), U1.9 (EXP), U2.1 (GND), U2.28 (GND), U2.29_1 (GND), U2.29_2 (GND), U2.29_3 (GND), U2.29_4 (GND), U2.29_5 (GND), U2.29_6 (GND), U2.29_7 (GND), U2.29_8 (GND), U2.29_9 (GND), U3.13 (GND), U4.1 (CTG), U4.4 (GND), U4.6 (QSTRT), U4.9 (EP)
GPIO8: R1.1, U2.10 (IO8)
I2C_PW: C1.1, C2.1, R1_PINH.2, R2_PINH.2, SENSOR2.2 (CSB), SENSOR2.6 (VDDIO), SENSOR2.8 (VDD), U2.17 (IO19)
INT_RTC: R1_PINH1.1, TPINTRTC.TP, U2.8 (IO0), U3.3 (SQW/!INT)
IO/BOOT: BOOT_BUTTON.3, BOOT_BUTTON.4, C6.1, R_BOOT.1, U2.15 (IO9)
IO/CHANGE: C10.1, CHANGE_BUTTON.3, CHANGE_BUTTON.4, R_CHANGE.1, U2.23 (IO15)
MISO: D6.2, J4.P7 (DAT0), R5.1, TPMISO.TP, U1.2 (DO(IO1)), U2.27 (IO2)
MOSI: D8.2, J1.14, J4.P3 (CMD), R6.1, TPMOSI.TP, U1.5 (DI(IO0)), U2.7 (IO7)
unnamed: J2.A5, R2-USB1.2
unnamed: J2.B5, R2-USB.1
unnamed: C1_BAT1.1, D2.1 (CATHODE), IC4.1 (VIN), IC4.3 (CE), Q1.2 (S)
unnamed: MCP73831.1 (STAT), R1_BAT.2
unnamed: C4.1, D3.2 (A), D4.1 (K)
unnamed: CHG_LED.C, R1_BAT.1
unnamed: MCP73831.5 (PROG), R2_BAT.2
unnamed: EPD_C12.2, J1.24
unnamed: EPD_C10.2, J1.22
unnamed: EPD_C8.2, J1.20
unnamed: EPD_C7.2, J1.19
unnamed: EPD_C6.2, J1.18
unnamed: EPD_C2.2, J1.5
unnamed: EPD_C1.2, J1.4
unnamed: C_DELAY.1, IC1.5 (CT)
unnamed: D7.1 (CATHODE), R_CAPACITOR.1
PREVGH: D5.1 (K), EPD_C9.2, J1.21
PREVGL: D4.2 (A), EPD_C11.2, J1.23
RESE: J1.3, Q3.2 (S), R3.2
RESE': R2.2, R3.1, SJ1.2
RESET: C5.1, IC1.1 (VOUT), RESET_BUTTON.3, RESET_BUTTON.4, R_RESET.1, U2.3 (EN)
RTC_RST: U2.16 (IO18), U3.4 (!RST)
RX: TPRX.TP, U2.24 (RXD0/GPIO17)
SCK: D9.2, J1.13, J4.P5 (CLK), R7.1, TPSCK.TP, U1.6 (CLK), U2.6 (IO6)
SCL: J3.4, R2_PINH.1, SENSOR2.4 (SCK), U2.20 (IO22), U3.16 (SCL), U4.7 (SCL)
SDA: J3.3, R1_PINH.1, SENSOR2.3 (SDI), U2.19 (IO21), U3.15 (SDA), U4.8 (SDA)
SRC: C4.2, D5.2 (A), L1.2, Q3.3 (D)
SS_SD: D12.2, J4.P2 (CD/DAT3), R10.1, U2.4 (IO4)
TX: TPTX.TP, U2.25 (TXD0/GPIO16)
USB_D+: D1.1 (I/O1_1), U2.14 (IO13)
USB_D-: D1.3 (I/O2_1), U2.13 (IO12)
VBAT: C2_BAT.1, MCP73831.3 (VBAT), Q1.3 (D), TPVBAT.TP, U4.2 (CELL), U4.3 (VDD)
VBUS: C1_BAT.1, C4_USB.1, C5_USB.1, CHG_LED.A, D1.5 (VBUS), D2.2 (ANODE), MCP73831.4 (VIN), PFMF.050.1.2, Q1.1 (G), R1_PWRUSB.2, TPVBUS.TP
VRTC: C8.1, C11.1, R_CAPACITOR.2, U3.14 (VBAT)
VUSB: J2.A4, J2.A9, J2.B4, J2.B9, PFMF.050.1.1
